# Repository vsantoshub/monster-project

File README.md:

<b> Real-time Thermal Stress Monitor </b>
<br />
This project was developed inside the Mechanical Engineering department in the Federal Univesity of Santa Catarina. <br />
Also this project played a critical role in a study of working condition inside poultry slaughterhouses in South Brazil. <br />
<br />
Some technologies used are listed below. <br />
<br />
Hardware: <br />
+ Xbee S3B radio module <br />
+ PCB specially designed to be as smaller as possible  <br />
+ Murata NXR NTX thermistors  <br />
+ Lithim-Ion battery powered modules (two months duration)  <br />

User-Interface: <br />
+ C# interface developed with Windows Forms framework <br />
+ The interface is programmatically built  <br />
+ Used Zigbee's proprietary API to communicate with the radios <br />
<br /><br />

<b>User Interface </b>
<br />
The project can be built normally using Microsoft Visual Studio. No external dependencies needed.
<br />
The user interface initially makes a search, to look for the radios registered in the network.
<br />
After this, the interface shows the temperature measurements, updated in each five minutes. <br />
The Zigbee radios are configured in the sleep mode, waking up every five minutes to sample the temperature. <br />

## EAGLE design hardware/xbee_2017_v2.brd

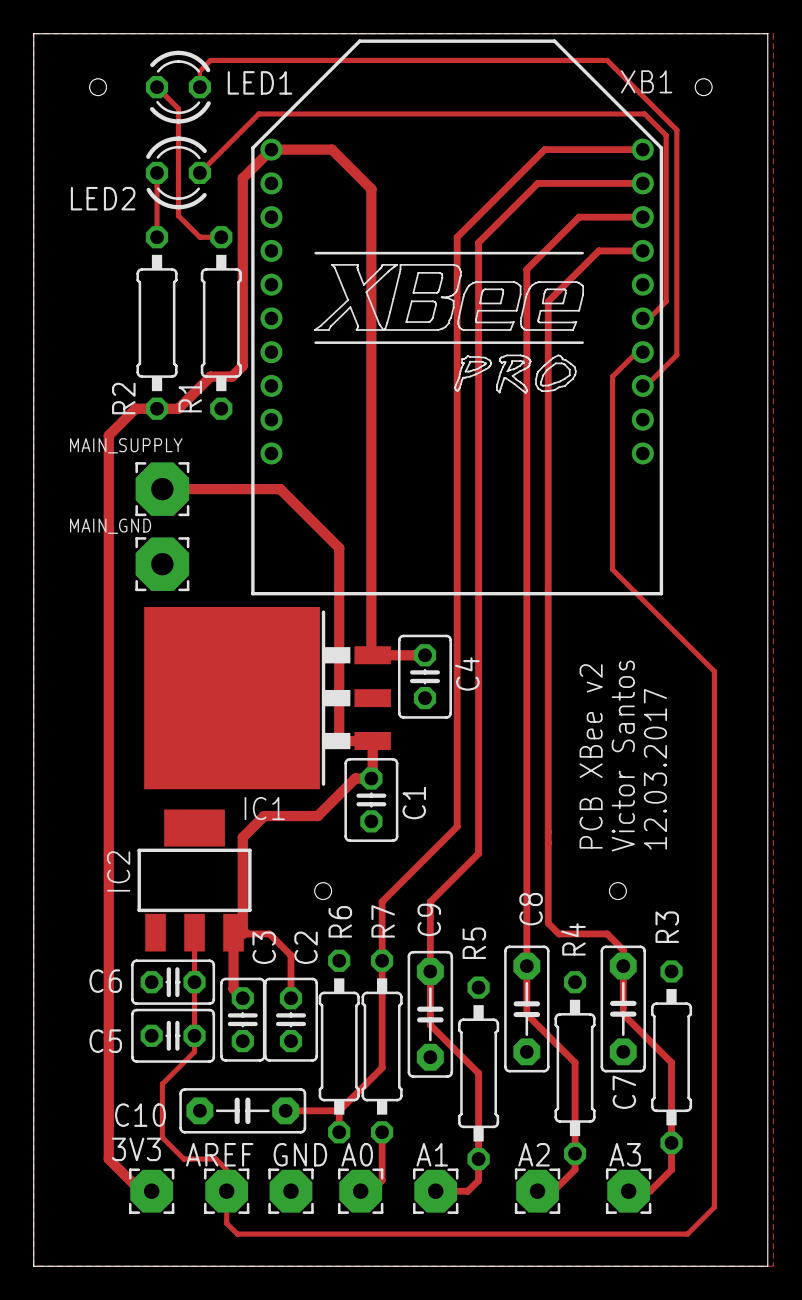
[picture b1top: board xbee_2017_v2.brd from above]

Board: 2 copper layers, 43.5 x 73.0 mm, 31 parts (0 on the bottom side), 13 nets.

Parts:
3V3: 2,54/0,9
A0, A1, A2, A3: 2,54/0,9
AREF: 2,54/0,9
C1, C3, C4, C5: 10uF/16V; C025-030X050
C2, C6: 220nF; C025-025X050
C7, C8, C9, C10: 470nF; C5B2.5
GND: 2,54/0,9
IC1: TO263-3
IC2: LM1117IMPX-3.3; SOT223
LED1, LED2: red; LED3MM
MAIN_GND: 3,17/1,3
MAIN_SUPPLY: 3,17/1,3
R1, R2: 470R; 0207/10
R3, R4, R5, R6, R7: 10k; 0207/10
XB1: XBEE-PRO

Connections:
GND: C1.2, C2.2, C3.2, C4.2, C5.2, C6.2, C7.1, C8.2, C9.2, C10.2, GND.1, IC1.2, IC2.1, MAIN_GND.1, R1.1, R3.2, R4.1, R5.2, R6.2, XB1.10
unnamed: LED1.K, R1.2
unnamed: LED2.A, R2.1
unnamed: LED2.K, XB1.15
unnamed: LED1.A, XB1.13
unnamed: A1.1, C9.1, R5.1, XB1.19
unnamed: C10.1, R6.1, R7.2, XB1.20
unnamed: A3.1, C7.2, R3.1, XB1.17
unnamed: A2.1, C8.1, R4.2, XB1.18
S$1: A0.1, R7.1
VCC: C1.1, C2.1, C3.1, IC1.1, IC2.3, MAIN_SUPPLY.1
VOUT_3.3: 3V3.1, C4.1, IC1.3, R2.2, XB1.1
VREF: AREF.1, C5.1, C6.1, IC2.2, XB1.14

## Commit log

2018-12-16 Initial commit for the monster-project repo.
    Further informations about the project can be found inside docs folder.
